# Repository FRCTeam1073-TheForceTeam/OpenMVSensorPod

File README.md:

# OpenMVSensorPod
Design files for building an OpenMV based sensor pod, including expansion boards and cases.

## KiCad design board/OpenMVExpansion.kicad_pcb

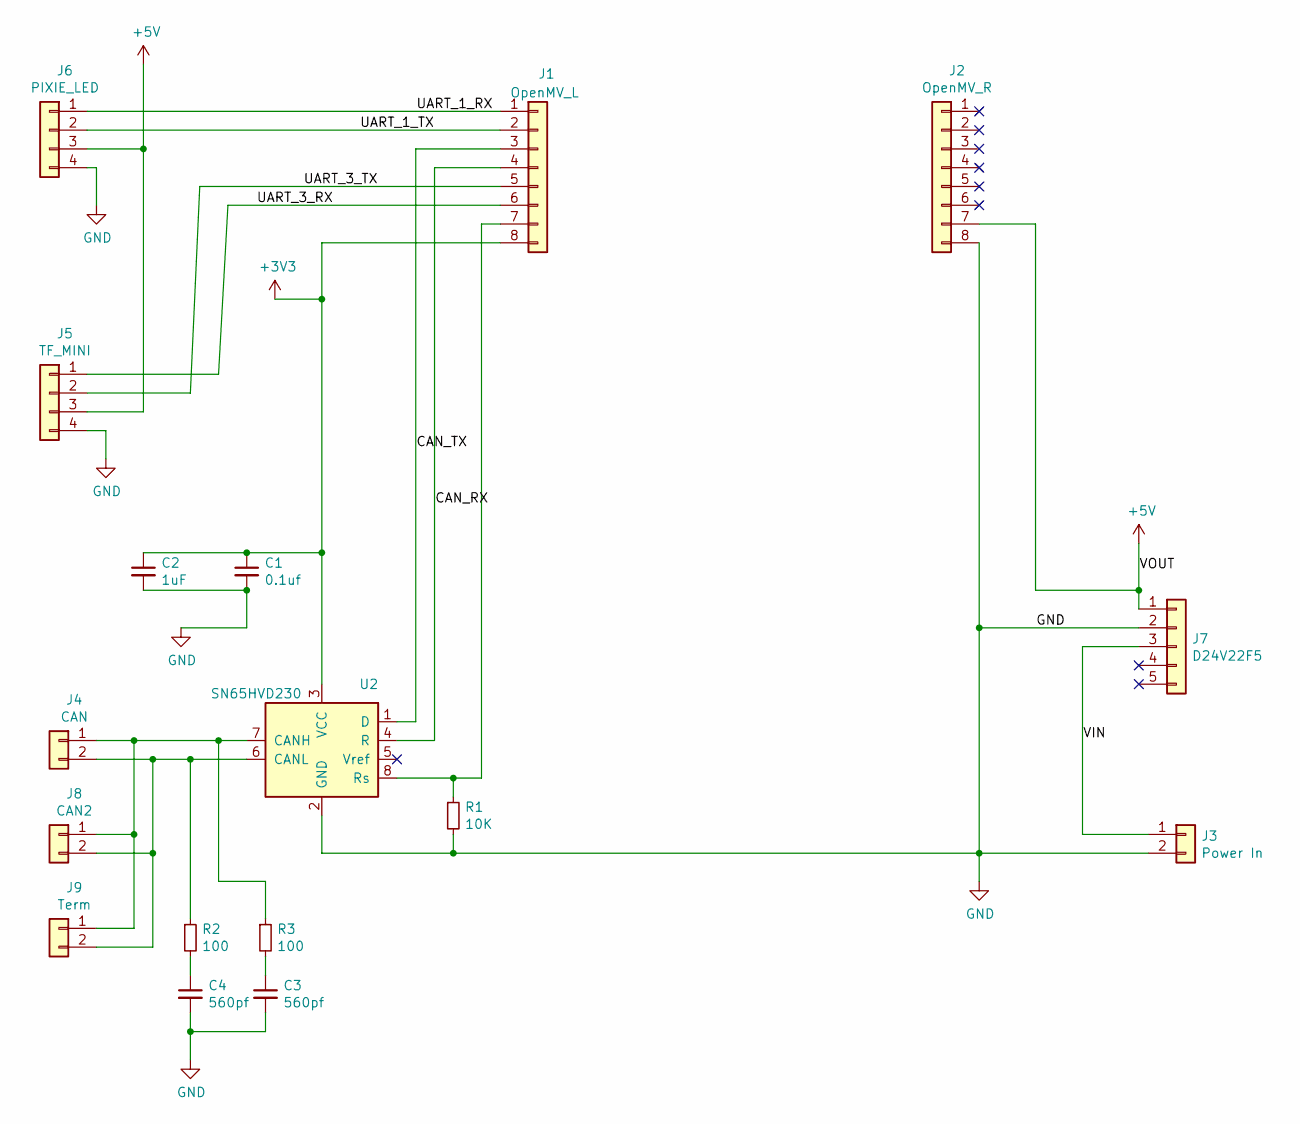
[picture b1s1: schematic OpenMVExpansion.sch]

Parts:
C1: 0.1uf; C_0603_1608Metric_Pad1.05x0.95mm_HandSolder
C2: 1uF; C_0603_1608Metric_Pad1.05x0.95mm_HandSolder
C3, C4: 560pf; C_0603_1608Metric_Pad1.05x0.95mm_HandSolder
J1: OpenMV_L; PinHeader_1x08_P2.54mm_Vertical
J2: OpenMV_R; PinHeader_1x08_P2.54mm_Vertical
J3: Power In; SolderWire-1.5sqmm_1x02_P6mm_D1.7mm_OD3mm
J4: CAN; SolderWire-0.75sqmm_1x02_P4.8mm_D1.25mm_OD2.3mm
J5: TF_MINI; PinHeader_1x04_P2.54mm_Vertical
J6: PIXIE_LED; SolderWire-0.75sqmm_1x04_P4.8mm_D1.25mm_OD2.3mm
J7: D24V22F5; PinHeader_1x05_P2.54mm_Vertical
J8: CAN2; SolderWire-0.75sqmm_1x02_P4.8mm_D1.25mm_OD2.3mm
J9: Term; PinHeader_1x02_P2.54mm_Vertical
R1: 10K; R_0603_1608Metric_Pad1.05x0.95mm_HandSolder
R2, R3: 100; R_0603_1608Metric_Pad1.05x0.95mm_HandSolder
U2: SN65HVD230; SOIC-8_3.9x4.9mm_P1.27mm

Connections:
+3V3: C1.1, C2.1, J1.8, U2.3 (VCC)
+5V: J2.7, J5.3, J6.3, J7.1
/CAN_RX: J1.4, U2.4 (R)
/CAN_TX: J1.3, U2.1 (D)
/UART_1_RX: J1.1, J6.1
/UART_1_TX: J1.2, J6.2
/UART_3_RX: J1.6, J5.1
/UART_3_TX: J1.5, J5.2
/VIN: J3.1, J7.3
GND: C1.2, C2.2, C3.2, C4.2, J2.8, J3.2, J5.4, J6.4, J7.2, R1.2, U2.2 (GND)
unnamed: C3.1, R3.2
unnamed: C4.1, R2.2
unnamed: J1.7, R1.1, U2.8 (Rs)
unnamed: J4.1, J8.1, J9.1, R3.1, U2.7 (CANH)
unnamed: J4.2, J8.2, J9.2, R2.1, U2.6 (CANL)

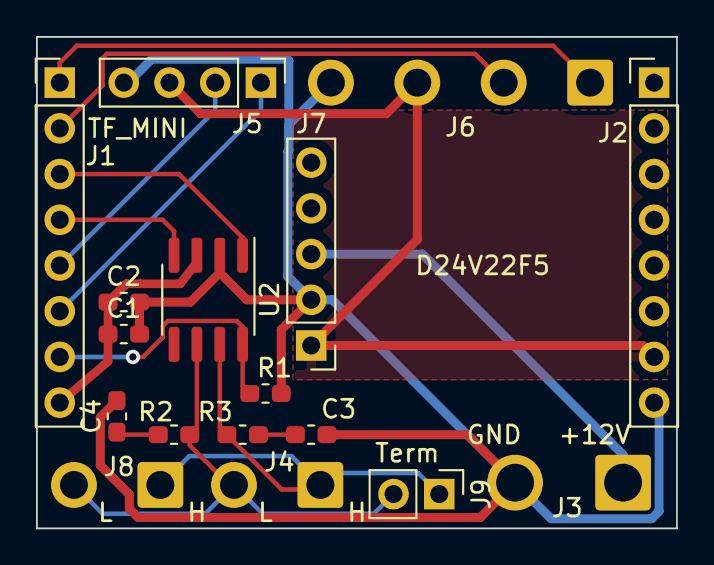
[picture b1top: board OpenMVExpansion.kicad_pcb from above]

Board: 2 copper layers, 35.6 x 27.3 mm, 17 parts (0 on the bottom side), 15 nets.

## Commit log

2021-01-19 OpenSCAD initial case file.
2021-01-22 Reorganized directory to separate case and board hardware. Added in cover from the prototype case design. Added holes for Pixie LED illuminator.
2021-01-22 Adding in schematic/board files (KiCAD) for expansion board that provides CANBus, Power Supply and Breakout for Pixie LED and TF-LIDAR MINI.
2021-01-23 Latest model to test and go over with EM group.
2021-01-23 Adjusting lens/mounting boss locations for OpenMV
2021-01-23 Adjusting lens baffle, opening up lidar screw holes, moving SD card slot..
